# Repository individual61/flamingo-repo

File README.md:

FLAMINGO!

My festival buddy.My fave programs are the damped harmonic oscillator, the bouncing ball, and green fire. 

First iteration was a perfboard mess, second was a custom PCBA I designed and assembled. Currently runs off a small, flat USB power bank.

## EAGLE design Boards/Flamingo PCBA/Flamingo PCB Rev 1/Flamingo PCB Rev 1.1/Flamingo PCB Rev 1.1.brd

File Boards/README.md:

This directory contains the board files.

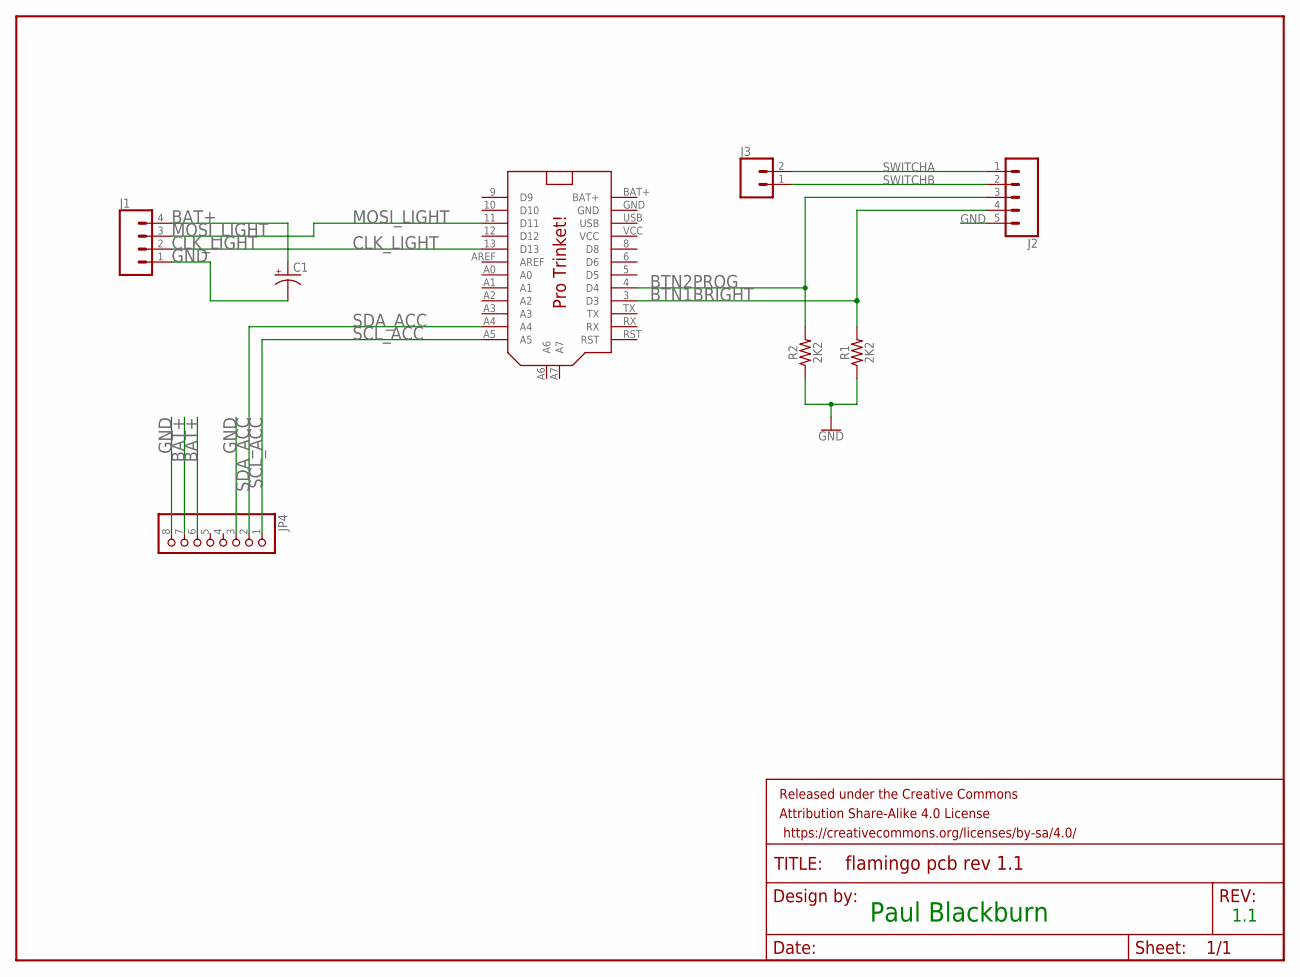
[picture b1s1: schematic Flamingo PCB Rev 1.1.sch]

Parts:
C1: CPOL-USE5-6; E5-6
FRAME1: FRAME-LETTER; CREATIVE_COMMONS
J1: CONN_04; 1X04
J2: CONN_05; 1X05
J3: CONN_02; 1X02
JP4: PINHD-1X8CLEANBIG; 1X08-CLEANBIG
R1, R2: 2K2; AXIAL-0.3
U$1: PRO_TRINKET; PROTRINKET

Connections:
BAT+: C1.+, J1.4, JP4.6, JP4.7, U$1.BAT+
BTN1BRIGHT: J2.4, R1.P$2 (2), U$1.3 (D3)
BTN2PROG: J2.3, R2.P$2 (2), U$1.4 (D4)
CLK_LIGHT: J1.2, U$1.13 (D13)
GND: C1.-, J1.1, J2.5, JP4.3, JP4.8, R1.P$1 (1), R2.P$1 (1), U$1.GND
MOSI_LIGHT: J1.3, U$1.11 (D11)
SCL_ACC: JP4.1, U$1.A5
SDA_ACC: JP4.2, U$1.A4
SWITCHA: J2.1, J3.2
SWITCHB: J2.2, J3.1
USB: U$1.USB
VCC: U$1.VCC

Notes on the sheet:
Paul Blackburn
1.1

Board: 2 copper layers, 9 parts (0 on the bottom side), 10 nets, no tracks yet.

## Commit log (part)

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2017-04-27 Initial Commit
    Created folder and file structure.
2017-04-27 Initialized Platformio for Flamingo Original
    Turned Platformio back on, which created two new files.
    The code compiles.
2017-04-27 Created Code/Flamingo Rev B
    Copied from Flamingo Original
2017-05-06 Refactored to multiple files
    Refactored the code into multiple files. There is a parameters.h for
    preprocessor definitions and extern variable declarations.
    loop() is now a hell of a lot tidier, as it should be.
    Compiles, but not tested.
2017-05-06 Move variables to PP defs, debug crashing
    Tidied up code, started addressing why the board built for BM 2016
    crashes. Added freeRAM() to diagnose. Consistently crashes when it
    reaches DHO_Sinetripes(). At that point free SRAM is around 147, and
    then I try to load a huge float table.
    Committing before trying to reduce the memory requirements of this
    program.
2017-05-06 Putting big things in PROGMEM
    Found why it was crashing. Free SRAM was 147 before moving a huge float
    table to PROGMEM and changing floats to ints (later dividing by 100.0),
    plus another PROGMEM change. I also put all setup() Serial strings in
    F().
    After all these changes, free SRAM is at 927!
2017-05-07 A few more PP refs and F()
    Moved a few more variables to PP defs and strings into F().
    Open issue: the blob program’s values follow the blob shape but
    flicker, therefore the array is not being read correctly from PROGMEM.
2017-05-07 Applied clang-format, tidied code
    Got clang-format config as I want it, and tidied up effects.cpp
2017-05-08 Added Sparkle/-Pink/-Fizz
    Added three programs.
    Sparkle: sparkles.
    Sparkle Pink: Sparkles pink.
    Sparke Pink Fizz: Reacts to acceleration and sparkles more. Needs
    adjustment.
    Also added some code to make single-pixel programs have their
2017-05-08 Added rolling time average (incomplete)
    Added a rolling time average. Needs better decay.
2017-05-09 SparkleFizz now works properly
    However, the exp() function slows things down a lot.
    Also, what I’m really looking for is jerk, not acceleration.
    Also, might address whole strand and not just one third of it.
2017-05-09 Trying to understand behavior of SparkleFizz
    SparkleFizz does not change gracefully from short to long random
    intervals. The issue seems to be with random(0, MAX) giving only 0 and
    MAX and nothing in between.
2017-05-10 Continued work on Sparkle Fizz
    The issue is that for max acceleration greater than MAX_G_SPARKLEFIZZ,
    it takes a while for acc_decayed to be equal to MAX_G_SPARKLEFIZZ. If
    acc_max is twice MAX_G_SPARKLEFIZZ, half of ACC_MAX_DECAY_RATE is spent
    at solid sparkle, leaving only the other half to get down to zero (for
    a linear decay).
    What’s needed is a separate decay timescale that starts at that moment,
2017-05-11 Increased SparkleFizz decay period to 16 s
    16 seconds and 2 g threshold seem to work well.
    Currently figuring out how to get a representative average of the
    acceleration derivative.
2017-05-12 Changed SparkleFizz rate to 20 seconds
    Looks better.
    At this point I’d say this program is “good enough”. The derivative of
    acceleration will have to wait. I’m not convinced it will be much of an
    improvement. Picking a derivative interval doesn’t seem
    straightforward.
    On to new programs.
2017-05-12 Tidied up code for merge back into master branch
2017-05-12 Created Physical version of DHO
    Finally revisited the DHO and acceleration equations. This allowed me
    to use the acceleration value in m/sˆ2 and ultimately express the ball
    position as a value centered on 0.0 when upright and -2.0 when upside
    down—exactly as one would expect for a mass on a spring at rest at x =
    0.0.
    This also allows me to change m, k and c without having to rescale
2017-05-13 Fixed accel functions: now really physical
    Found I had used acc_now instead of m*a in the integration of the
    equation of motion.
    getBallPosition() now returns 0 when upright and -2.0 when inverted, no
    matter what parameters are chosen for m, k and c.
    Parameters might need a little tweaking.
2017-05-13 Small tweaks for physical DHO
2017-05-15 Worked on DHO Fade and Comet; added utils.cpp/h
    Both DHO Fade and Comet are unsatisfactory. Fade has gaps when the ball
    moves too fast to register on all pixels, and Comet doesn’t seem to
    display the trail, no matter how long I make the history.
    Added utils.cpp/h for stuff like freeRam().
    Renamed setPixelByIndex to setPixelByStrandIndex for clarity.
    Added fadeWholeStrip(float fade_coef) and void
2017-05-20 Timing getballposition()
    Nope, not the cause of the delay. So is it the Dotstar library?
2017-05-20 DHO_Fade() is only 7 ms period, yet has gaps
    Will FastLED help? fadeWholeStrip() was the biggest contributor, at 7
    ms.
2017-05-22 First pass, untested, compiles
    As described. Likely nothing will work.
2017-05-22 FastLED transition cleanup continues
    My LED color order was wrong, so Flamingo pink looked too blue. Now
    things are as they should be. DHO_Comet is not working but I’m not too
    tied to it anyway. Can probably be fixed easily.
2017-05-22 Changed random() to random8/16()
    Also removed any mention of Adafruit Dotstar library
2017-05-23 Created programs/ dir
    effects.cpp was getting too long. Created programs-common.h and .cpp
    Transition to FastLED() is complete, save for some tweaks and
    adaptation.
2017-05-23 Added sparks to Fire With Palette
    Not bad at all:
    // No more than N sparks at a time, N could be around 5
    // Created with low probability every frame
    // Sparks ascend at constant different and random rate (found to be
    best to go 2 and 3 pixels per frame)
    // Sparks can die before reaching the top. They are born with "pixels
2017-05-24 Added Bouncing Balls. Totally does not work.
2017-05-24 Bouncing balls still not working
    Each ball is slower than the next. Need to check how timing intervals
    for RK are set.
2017-05-25 Bouncing Ball works. Code cleanup.
    Got BB to work, sort of. One ball looks better than more.
    Cleaning up programs for LiB.
2017-05-25 Added rainbow.cpp; pre-release for LIB2017
    Changed to FastLED’s rainbow functions. Used them in DHO Rainbow.
    Kept original fire because it has more yellow than a rgb -> grb swapped
    pallette fire. Added sparks to it. Added pink fire. Added rainbow fire.
    OMG.
2017-05-25 Initial totem testing
    Cleanup, F() macros, return if stolen intro.
2017-05-25 Small fixes for Totem
    Totem’s accelerometer is upside down. That explains A LOT.
2017-05-26 Added RUN_ON_TOTEM switch
    Switches between the accelerometer calibration of the testbed or the
    Totem.
2017-05-26 Made fire rainbow slowly cycle pallette.
    my god it’s full of stars
2017-05-26 Release candidate for LiB 2017
    Set acc cal for Totem.
2017-07-27 Added components to schematic
    Nothing connected to nets yet.
2017-07-29 Completed preliminary component layout
    Decided to just glue the 5 wires from the remote and 4 for the lights
    to the underside of the PCB.
2017-08-24 Changes for bike strip
    Made changes so it can be used on the bike. Fire is too slow, no time
    to fix.
2018-01-13 Probably moving away from Eagle...
    This may be the last commit with Eagle files
2018-02-05 Starting to create Rev 2
2018-02-06 First pass of battery charging section complete
    Still needs another pass for component and value selection.
2020-10-03 Adding first sub-sheets
    Arduino
    Battery Charger
    IMU
    Power
2020-10-07 PCB: bringing in symbols, re-making battery charger sheet, still has todo
2020-10-08 Advanced schematic for battery charger
    To do:
    * Find a better connector for the switch than a JST PH2
    * Check the polarity of the battery connector w.r.t. Adafruit batteries.
    *Assign footprints
2020-10-08 Fixed footprint libraries to v5, added some footprints
2020-10-09 Worked on Power board mainly.
    Still have to resolve the power sharing.
2020-10-10 NOSTUFF 5V LDO bc not needed. Added Sch diode on 5v LDO.
2020-10-12 Moved Battery Charger sheet into Power sheet
    Right before addition of power sharing mosfet, maybe
2020-10-13 More work on Arduino schematic, created button board schematic
    Button board schematic should probably be a separate project
2020-10-13 More work on Arduino sheet
    Added V_BUS sensing, removed V_BAT sensing bc it would be a discharge situation. Assigned some lines to pins. Added placeholders for headers.
2020-10-13 Tidy up
2020-10-18 Added Button Remote project
2022-05-20 Undocumented changes
2022-05-20 Created through hole files, did not do anything
2022-05-25 Fixed compilation issue by copying I2Cdevlib files into lib/ and discovered rewrite is very incomplete womp womp
    https://community.platformio.org/t/library-header-not-found-installed-library-seems-to-be-empty/27841/5
2022-05-25 It finally builds. Turns out going with main branch instead of dev was a bad idea. Or something
    Fixed it by copy pasting in code that seems to have been accidentally nuked, harmonic_oscillator.cpp.
2022-05-25 A commit just to get things synced with .gitignore
2022-08-01 Got interrupts on all 3 butotns worksing
2022-08-01 Re-adding Bike Flamingo after wiping repository due to broken stash
2022-08-01 Testing lights
2022-08-01 Sparkles work great
2022-08-02 Started creating carrier board schematic for Bike Flamingo
2022-08-02 Finished Bike Flamingo board Rev 1
2022-08-03 As ordered from JCLPCB with generated gerbers
2022-08-03 Got the skeleton of a good architecture, start to migrate/merge w Flamingo
    Have 3 buttons with ISR, program index, demonstrated sparkle and rainbow cycle fire.
    Time to merge and generalize code.
2022-08-03 Finally got brightness array to pass compile
2022-08-03 First successful compilatiion after bringing legacy code into bike flamingo
2022-08-03 Found the memory corruption location, will have to adapt to arbitrary number of strands
    The issue is here
    void setPixelByStrandIndex(uint16_t index, CRGB color)
    {
    if ((index >= 0) && (index < NUMPERSTRAND))
    {
    // index goes from 0 to NUMPERSTRAND - 1
2022-08-03 Fixed the bug with the memory corruption, commented out a lot of print statements
2022-08-04 Added some notes on power: the battery connector is not likely to be useful
    Since if USB is unplugged, the only route to the LED VCC (VBUS) is through the 5 V regulator. This is also true if a battery backpack is used.
    Does it make sense to put the batt connector on the VUSB line? Not really, because then the Arduino just sees unregulated batt... which is OK for a LiPo I guess.
    Does it make sense to change the LEDs to use VBAT? With VBAT and no USB present, the LEDS get direct battery and the arduino gets regulated output. With USB and no VBAT the LEDs dont see VBUS unless 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
2022-08-11 Found issues with Rev 1 Bike Flamingo, made Rev 2, added time()
2022-09-20 Last commit before switching to Pixelblaze
    When a better solution comes along, you have to be able to switch, even if it means not using months and months of your own work...
2023-04-28 Carrier board for Arduino Nano 33 BLE Rev 2 sent to fab
2023-05-03 Started from scratch. Buttons and timing working.
2023-05-04 Damped Harmonic Oscillator is working
    Found good settings for 120 BPM bounce. Also fixed the ball being waaaay far out when it is first run, caused by the timing interval not being updated during setup()
2023-05-07 A little more advancement on harmonic oscillator, beginnings of a program structure, etc
2023-05-08 Removed while(!Serial), prevented loop start until connected to apparently
2023-05-09 Implemented Sparkle
2023-05-16 A mess, but first working version of Fire Green Original
2023-05-17 Completed first successful Rainbow Fire
2023-05-17 Converted Synchronized Random Numbers Pixelblaze program
2023-05-17 Completed several Sync Rand Num settings
2023-05-19 Added compass (inop) and gflash
2023-05-23 Finished adjusting max brightness for all programs
2023-05-23 Finished brightness calibration for max current and levels
2023-05-25 measured two batteries on max burn with this code
2023-05-26 As taken to LIB 2023!
2023-05-30 todo

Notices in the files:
parts and their libraries:
SparkFun-Aesthetics: Licensing: Creative Commons ShareAlike 4.0 International - https://creativecommons.org/licenses/by-sa/4.0
SparkFun-Aesthetics: Released under the Creative Commons Attribution Share-Alike 4.0 License
SparkFun-Aesthetics: https://creativecommons.org/licenses/by-sa/4.0
